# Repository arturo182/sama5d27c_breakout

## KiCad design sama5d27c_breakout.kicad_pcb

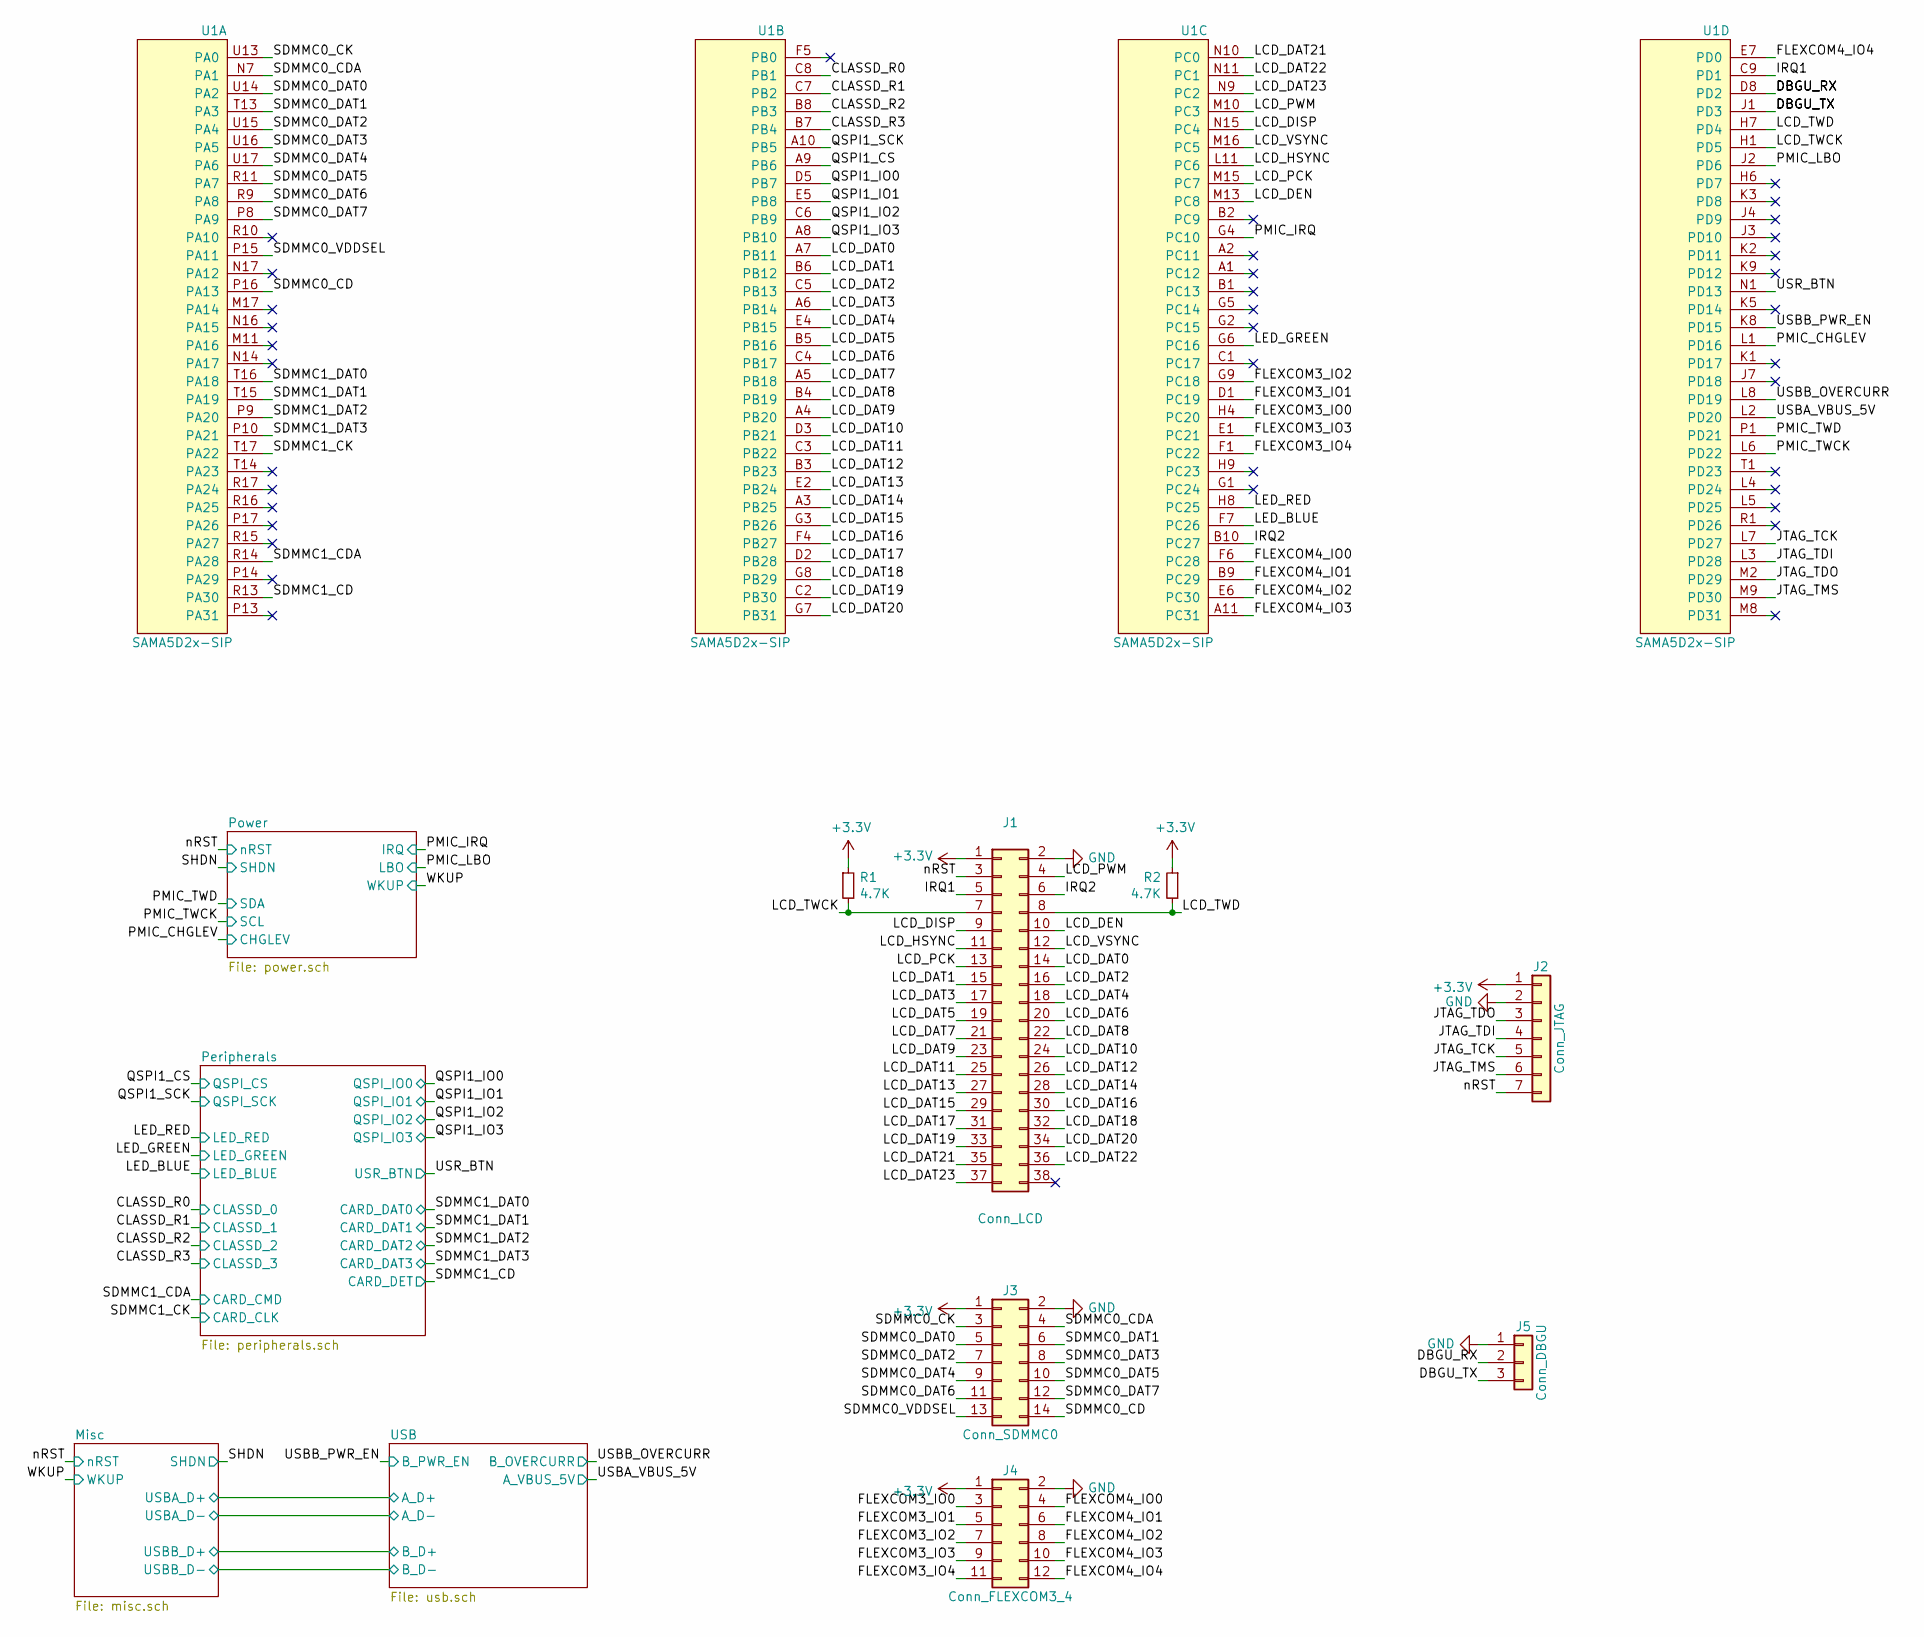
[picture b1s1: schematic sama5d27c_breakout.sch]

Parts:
J1: Conn_LCD; PinHeader_2x19_P1.27mm_Vertical_SMD
J2: Conn_JTAG; PinHeader_1x07_P2.54mm_Vertical
J3: Conn_SDMMC0; PinHeader_2x07_P2.54mm_Vertical
J4: Conn_FLEXCOM3_4; PinHeader_2x06_P2.54mm_Vertical
J5: Conn_DBGU; PinHeader_1x03_P2.54mm_Vertical
R1, R2: 4.7K; R_0603_1608Metric
U1: SAMA5D2x-SIP; TFBGA-289_17x17_14.0x14.0mm

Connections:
/CLASSD_R0: U1.C8 (PB1); also elsewhere on the board
/CLASSD_R1: U1.C7 (PB2); also elsewhere on the board
/CLASSD_R2: U1.B8 (PB3); also elsewhere on the board
/CLASSD_R3: U1.B7 (PB4); also elsewhere on the board
/DBGU_RX: J5.2, U1.D8 (PD2)
/DBGU_TX: J5.3, U1.J1 (PD3)
/FLEXCOM3_IO0: J4.3, U1.H4 (PC20)
/FLEXCOM3_IO1: J4.5, U1.D1 (PC19)
/FLEXCOM3_IO2: J4.7, U1.G9 (PC18)
/FLEXCOM3_IO3: J4.9, U1.E1 (PC21)
/FLEXCOM3_IO4: J4.11, U1.F1 (PC22)
/FLEXCOM4_IO0: J4.4, U1.F6 (PC28)
/FLEXCOM4_IO1: J4.6, U1.B9 (PC29)
/FLEXCOM4_IO2: J4.8, U1.E6 (PC30)
/FLEXCOM4_IO3: J4.10, U1.A11 (PC31)
/FLEXCOM4_IO4: J4.12, U1.E7 (PD0)
/IRQ1: J1.5, U1.C9 (PD1)
/IRQ2: J1.6, U1.B10 (PC27)
/JTAG_TCK: J2.5, U1.L7 (PD27)
/JTAG_TDI: J2.4, U1.L3 (PD28)
/JTAG_TDO: J2.3, U1.M2 (PD29)
/JTAG_TMS: J2.6, U1.M9 (PD30)
/LCD_DAT0: J1.14, U1.A7 (PB11)
/LCD_DAT1: J1.15, U1.B6 (PB12)
/LCD_DAT2: J1.16, U1.C5 (PB13)
/LCD_DAT3: J1.17, U1.A6 (PB14)
/LCD_DAT4: J1.18, U1.E4 (PB15)
/LCD_DAT5: J1.19, U1.B5 (PB16)
/LCD_DAT6: J1.20, U1.C4 (PB17)
/LCD_DAT7: J1.21, U1.A5 (PB18)
/LCD_DAT8: J1.22, U1.B4 (PB19)
/LCD_DAT9: J1.23, U1.A4 (PB20)
/LCD_DAT10: J1.24, U1.D3 (PB21)
/LCD_DAT11: J1.25, U1.C3 (PB22)
/LCD_DAT12: J1.26, U1.B3 (PB23)
/LCD_DAT13: J1.27, U1.E2 (PB24)
/LCD_DAT14: J1.28, U1.A3 (PB25)
/LCD_DAT15: J1.29, U1.G3 (PB26)
/LCD_DAT16: J1.30, U1.F4 (PB27)
/LCD_DAT17: J1.31, U1.D2 (PB28)
/LCD_DAT18: J1.32, U1.G8 (PB29)
/LCD_DAT19: J1.33, U1.C2 (PB30)
/LCD_DAT20: J1.34, U1.G7 (PB31)
/LCD_DAT21: J1.35, U1.N10 (PC0)
/LCD_DAT22: J1.36, U1.N11 (PC1)
/LCD_DAT23: J1.37, U1.N9 (PC2)
/LCD_DEN: J1.10, U1.M13 (PC8)
/LCD_DISP: J1.9, U1.N15 (PC4)
/LCD_HSYNC: J1.11, U1.L11 (PC6)
/LCD_PCK: J1.13, U1.M15 (PC7)
/LCD_PWM: J1.4, U1.M10 (PC3)
/LCD_TWCK: J1.7, R1.2, U1.H1 (PD5)
/LCD_TWD: J1.8, R2.2, U1.H7 (PD4)
/LCD_VSYNC: J1.12, U1.M16 (PC5)
/LED_BLUE: U1.F7 (PC26); also elsewhere on the board
/LED_GREEN: U1.G6 (PC16); also elsewhere on the board
/LED_RED: U1.H8 (PC25); also elsewhere on the board
/PMIC_CHGLEV: U1.L1 (PD16); also elsewhere on the board
/PMIC_IRQ: U1.G4 (PC10); also elsewhere on the board
/PMIC_LBO: U1.J2 (PD6); also elsewhere on the board
/PMIC_TWCK: U1.L6 (PD22); also elsewhere on the board
/PMIC_TWD: U1.P1 (PD21); also elsewhere on the board
/QSPI1_CS: U1.A9 (PB6); also elsewhere on the board
/QSPI1_IO0: U1.D5 (PB7); also elsewhere on the board
/QSPI1_IO1: U1.E5 (PB8); also elsewhere on the board
/QSPI1_IO2: U1.C6 (PB9); also elsewhere on the board
/QSPI1_IO3: U1.A8 (PB10); also elsewhere on the board
/QSPI1_SCK: U1.A10 (PB5); also elsewhere on the board
/SDMMC0_CD: J3.14, U1.P16 (PA13)
/SDMMC0_CDA: J3.4, U1.N7 (PA1)
/SDMMC0_CK: J3.3, U1.U13 (PA0)
/SDMMC0_DAT0: J3.5, U1.U14 (PA2)
/SDMMC0_DAT1: J3.6, U1.T13 (PA3)
/SDMMC0_DAT2: J3.7, U1.U15 (PA4)
/SDMMC0_DAT3: J3.8, U1.U16 (PA5)
/SDMMC0_DAT4: J3.9, U1.U17 (PA6)
/SDMMC0_DAT5: J3.10, U1.R11 (PA7)
/SDMMC0_DAT6: J3.11, U1.R9 (PA8)
/SDMMC0_DAT7: J3.12, U1.P8 (PA9)
/SDMMC0_VDDSEL: J3.13, U1.P15 (PA11)
/SDMMC1_CD: U1.R13 (PA30); also elsewhere on the board
/SDMMC1_CDA: U1.R14 (PA28); also elsewhere on the board
/SDMMC1_CK: U1.T17 (PA22); also elsewhere on the board
/SDMMC1_DAT0: U1.T16 (PA18); also elsewhere on the board
/SDMMC1_DAT1: U1.T15 (PA19); also elsewhere on the board
/SDMMC1_DAT2: U1.P9 (PA20); also elsewhere on the board
/SDMMC1_DAT3: U1.P10 (PA21); also elsewhere on the board
/USBA_VBUS_5V: U1.L2 (PD20); also elsewhere on the board
/USBB_OVERCURR: U1.L8 (PD19); also elsewhere on the board
/USBB_PWR_EN: U1.K8 (PD15); also elsewhere on the board
/USR_BTN: U1.N1 (PD13); also elsewhere on the board
/nRST: J1.3, J2.7; also elsewhere on the board
GND: J1.2, J2.2, J3.2, J4.2, J5.1; also elsewhere on the board

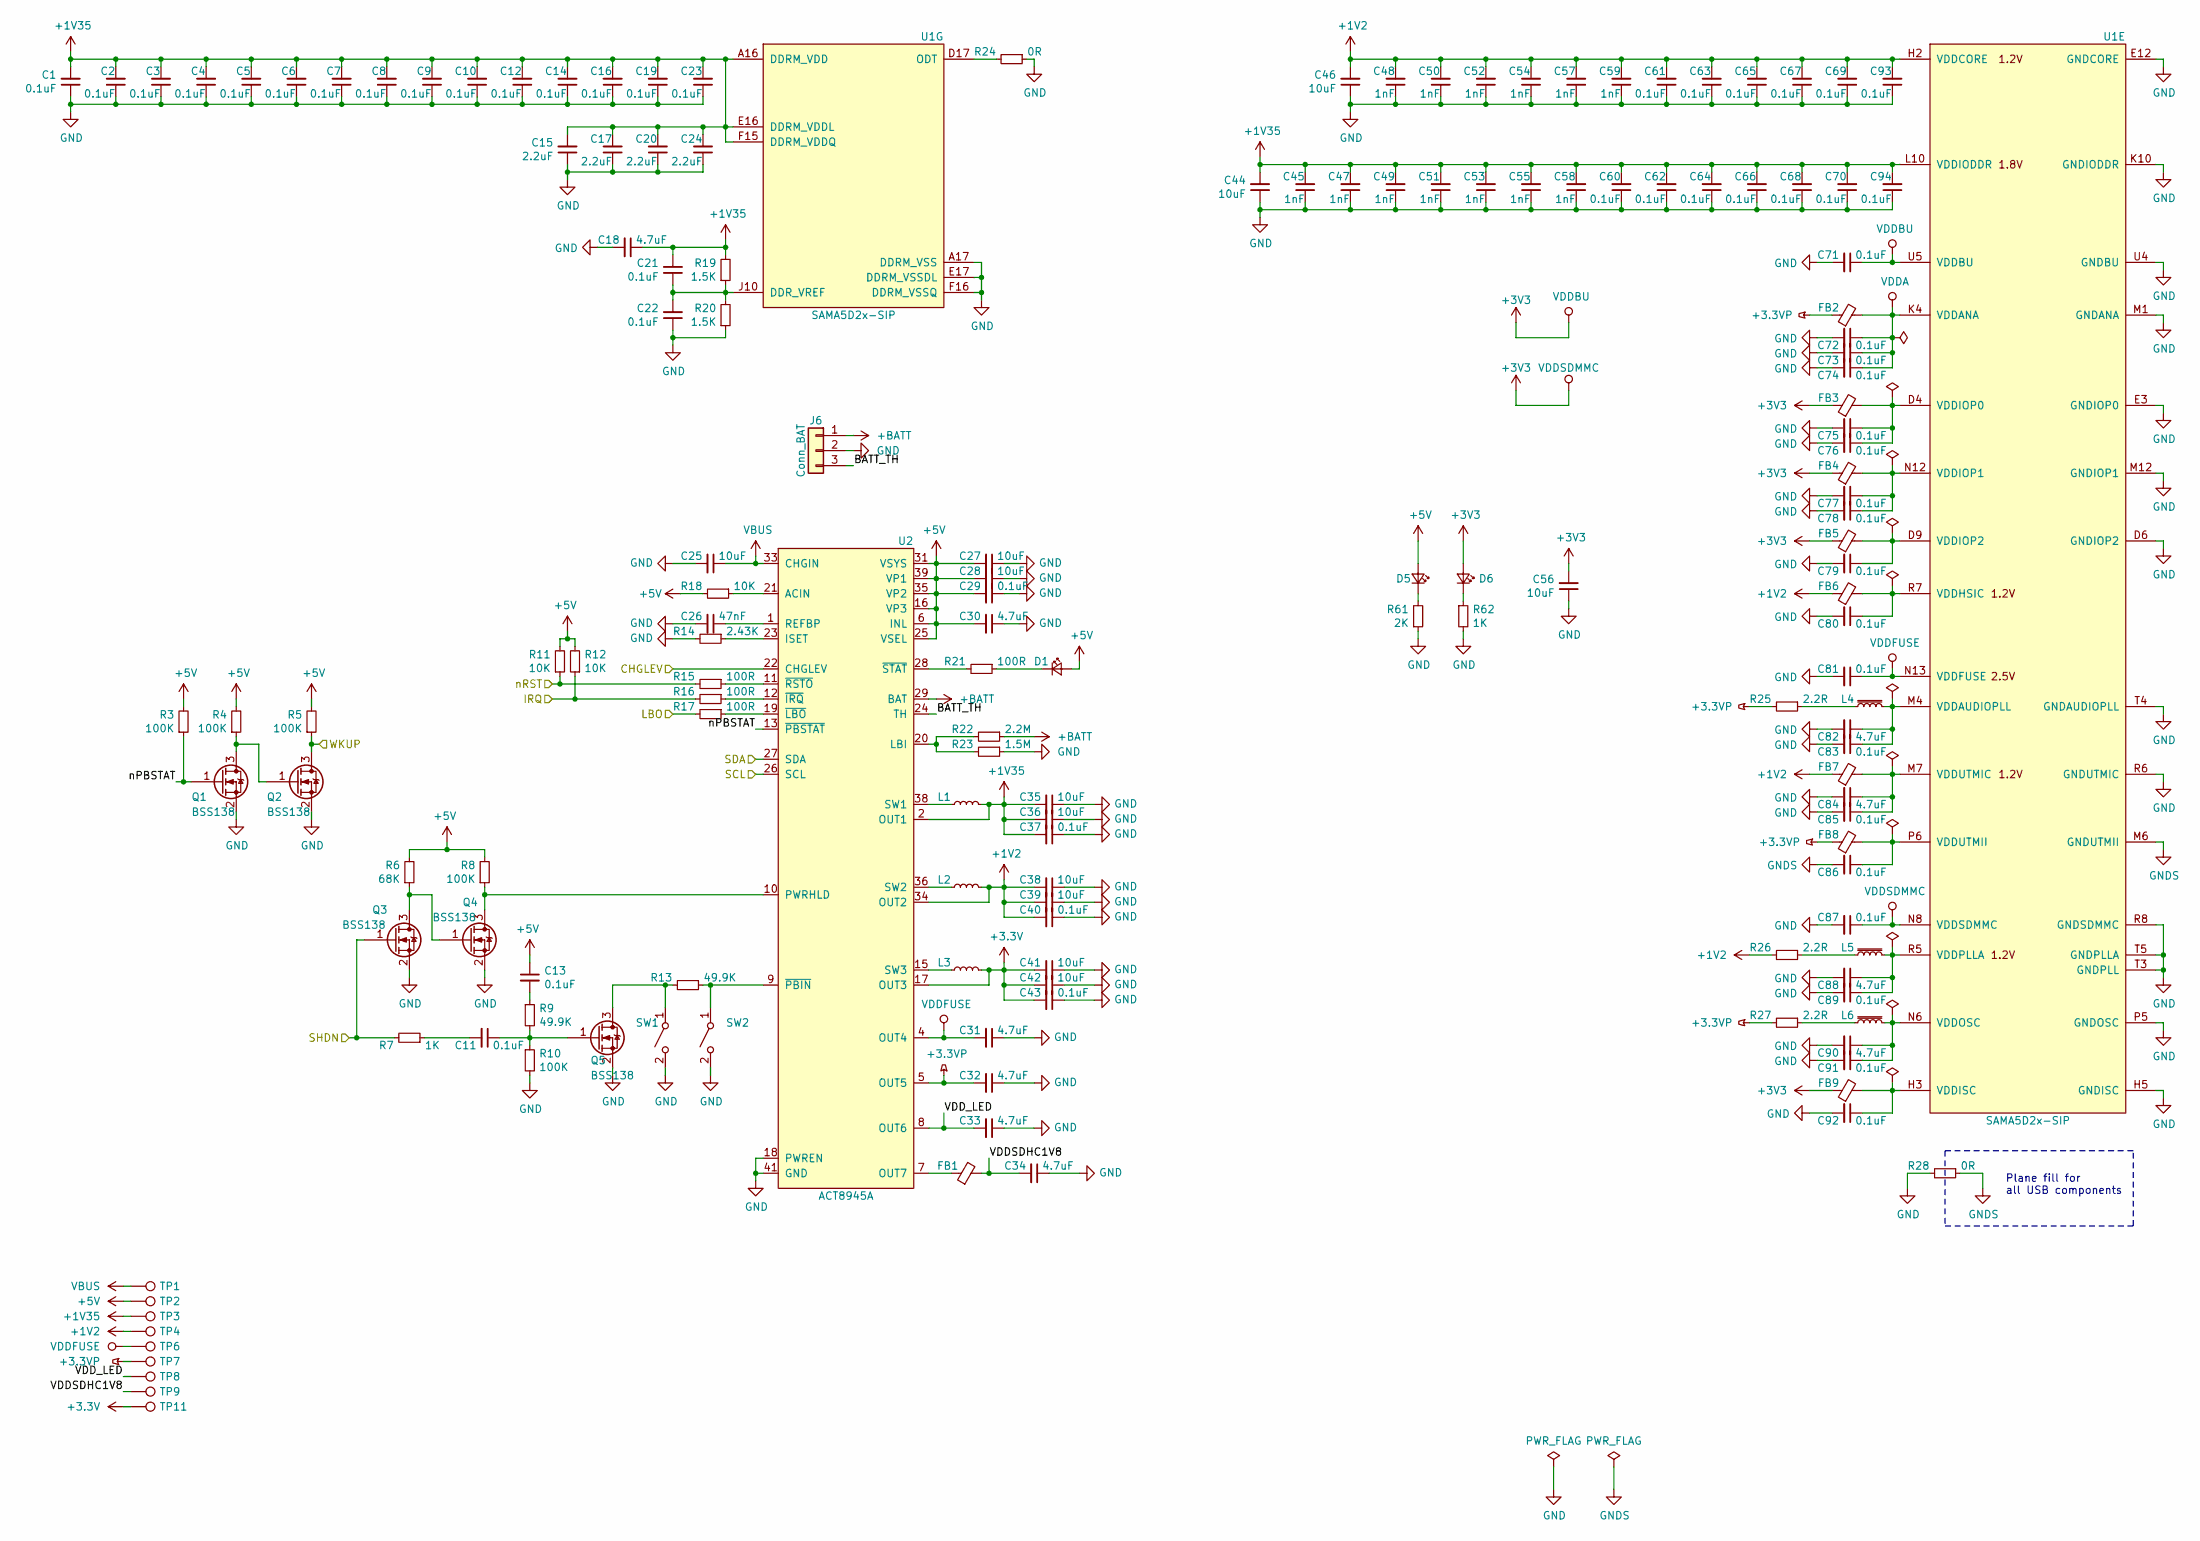
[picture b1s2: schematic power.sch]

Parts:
C1, C2, C3, C4, C5, C6, C7, C8, C9, C10, C11, C12, C13, C14, C16, C19, C21, C22, C23, C29, C37, C40, C43, C60, C61, C62, C63, C64, C65, C66, C67, C68, C69, C70, C71, C72, C73, C74, C75, C76, C77, C78, C79, C80, C81, C83, C85, C86, C87, C89, C91, C92, C93, C94: 0.1uF; C_0402_1005Metric
C15, C17, C20, C24: 2.2uF; C_0402_1005Metric
C18, C30, C31, C32, C33, C34, C82, C84, C88, C90: 4.7uF; C_0402_1005Metric
C25, C27, C28, C35, C36, C38, C39, C41, C42, C44, C46, C56: 10uF; C_0402_1005Metric
C26: 47nF; C_0402_1005Metric
C45, C47, C48, C49, C50, C51, C52, C53, C54, C55, C57, C58, C59: 1nF; C_0402_1005Metric
D1: LED_CHARGE; LED_0603_1608Metric
D5: LED_5V; LED_0603_1608Metric
D6: LED_3V; LED_0603_1608Metric
FB1: BLM18PG181SN1D; L_0603_1608Metric
FB2, FB3, FB4, FB5, FB6, FB7, FB8, FB9: BLM18PG300SN1D; L_0603_1608Metric
J6: Conn_BAT; PinHeader_1x03_P2.54mm_Vertical
L1, L2, L3: LQM2HPN2R2MG0L; L_Taiyo-Yuden_MD-3030
L4, L5, L6: MLZ1608N100L; L_0603_1608Metric
Q1, Q2, Q3, Q4, Q5: BSS138; SOT-23
R3, R4, R5, R8, R10: 100K; R_0603_1608Metric
R6: 68K; R_0603_1608Metric
R7, R62: 1K; R_0603_1608Metric
R9, R13: 49.9K; R_0603_1608Metric
R11, R12, R18: 10K; R_0603_1608Metric
R14: 2.43K; R_0603_1608Metric
R15, R16, R17, R21: 100R; R_0603_1608Metric
R19, R20: 1.5K; R_0603_1608Metric
R22: 2.2M; R_0603_1608Metric
R23: 1.5M; R_0603_1608Metric
R24, R28: 0R; R_0603_1608Metric
R25, R26, R27: 2.2R; R_0603_1608Metric
R61: 2K; R_0603_1608Metric
SW1: SW_WAKEUP; SW_SPST_FSMSM
SW2: SW_RESET; SW_SPST_FSMSM
TP1: TP_VBUS; TestPoint_Pad_D1.5mm
TP2: TP_5V; TestPoint_Pad_D1.5mm
TP3: TP_1.35V; TestPoint_Pad_D1.5mm
TP4: TP_1.2V; TestPoint_Pad_D1.5mm
TP6: TP_VDDFUSE; TestPoint_Pad_D1.5mm
TP7: TP_3.3VP; TestPoint_Pad_D1.5mm
TP8: TP_VDD_LED; TestPoint_Pad_D1.5mm
TP9: TP_VDDSDHC1V8; TestPoint_Pad_D1.5mm
TP11: TP_VDDSDMMC; TestPoint_Pad_D1.5mm
U1: SAMA5D2x-SIP; TFBGA-289_17x17_14.0x14.0mm
U2: ACT8945A; QFN-40-1EP_5x5mm_P0.4mm_EP3.6x3.6mm

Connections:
+1V2: C38.2, C39.2, C40.2, C46.2, C48.2, C50.2, C52.2, C54.2, C57.2, C59.2, C61.2, C63.2, C65.2, C67.2, C69.2, C93.2, FB6.1, FB7.1, L2.1, R26.2, TP4.1, U1.D7 (VDDCORE), U1.E9 (VDDCORE), U1.H2 (VDDCORE), U1.L12 (VDDCORE), U1.P7 (VDDCORE), U1.U3 (VDDCORE), U2.34 (OUT2)
+1V35: C1.2, C2.2, C3.2, C4.2, C5.2, C6.2, C7.2, C8.2, C9.2, C10.2, C12.2, C14.2, C15.2, C16.2, C17.2, C18.1, C19.2, C20.2, C21.2, C23.2, C24.2, C35.2, C36.2, C37.2, C44.2, C45.2, C47.2, C49.2, C51.2, C53.2, C55.2, C58.2, C60.2, C62.2, C64.2, C66.2, C68.2, C70.2, C94.2, L1.1, R19.2, TP3.1, U1.A16 (DDRM_VDD), U1.B16 (DDRM_VDD), U1.C16 (DDRM_VDD), U1.D16 (DDRM_VDD), U1.E8 (VDDIODDR), U1.E11 (VDDIODDR), U1.E15 (DDRM_VDD), U1.E16 (DDRM_VDDL), U1.F15 (DDRM_VDDQ), U1.G12 (VDDIODDR), U1.G15 (DDRM_VDDQ), U1.G17 (DDRM_VDD), U1.H10 (VDDIODDR), U1.H15 (DDRM_VDDQ), U1.J8 (VDDIODDR), U1.J15 (DDRM_VDDQ), U1.J17 (DDRM_VDD), U1.K15 (DDRM_VDDQ), U1.L10 (VDDIODDR), U1.L14 (VDDIODDR), U1.L15 (DDRM_VDDQ), U1.L16 (DDRM_VDD), U2.2 (OUT1)
+3.3VP: C32.2, FB2.1, FB8.1, R25.2, R27.2, TP7.1, U2.5 (OUT5)
+5V: C13.1, C27.2, C28.2, C29.2, C30.2, D1.2 (A), D5.2 (A), R3.2, R4.2, R5.2, R6.2, R8.2, R11.2, R12.2, R18.2, TP2.1, U2.6 (INL), U2.16 (VP3), U2.25 (VSEL), U2.31 (VSYS), U2.32 (VSYS), U2.35 (VP2), U2.39 (VP1); also elsewhere on the board
+BATT: J6.1, R22.1, U2.29 (BAT), U2.30 (BAT)
/PMIC_CHGLEV: U2.22 (CHGLEV); also elsewhere on the board
/PMIC_IRQ: R12.1, R16.2; also elsewhere on the board
/PMIC_LBO: R17.2; also elsewhere on the board
/PMIC_TWCK: U2.26 (SCL); also elsewhere on the board
/PMIC_TWD: U2.27 (SDA); also elsewhere on the board
/Power/BATT_TH: J6.3, U2.24 (TH)
/Power/VDDSDHC1V8: C34.2, FB1.2, TP9.1
/Power/VDD_LED: C33.2, TP8.1, U2.8 (OUT6)
/Power/nPBSTAT: Q1.1 (G), R3.1, U2.13 (~PBSTAT~)
/SHDN: Q3.1 (G), R7.2; also elsewhere on the board
/WKUP: Q2.3 (D), R5.1; also elsewhere on the board
/nRST: R11.1, R15.2; also elsewhere on the board
GND: C1.1, C2.1, C3.1, C4.1, C5.1, C6.1, C7.1, C8.1, C9.1, C10.1, C12.1, C14.1, C15.1, C16.1, C17.1, C18.2, C19.1, C20.1, C22.1, C23.1, C24.1, C25.2, C26.2, C27.1, C28.1, C29.1, C30.1, C31.1, C32.1, C33.1, C34.1, C35.1, C36.1, C37.1, C38.1, C39.1, C40.1, C41.1, C42.1, C43.1, C44.1, C45.1, C46.1, C47.1, C48.1, C49.1, C50.1, C51.1, C52.1, C53.1, C54.1, C55.1, C56.1, C57.1, C58.1, C59.1, C60.1, C61.1, C62.1, C63.1, C64.1, C65.1, C66.1, C67.1, C68.1, C69.1, C70.1, C71.2, C72.2, C73.2, C74.2, C75.2, C76.2, C77.2, C78.2, C79.2, C80.2, C81.2, C82.2, C83.2, C84.2, C85.2, C87.2, C88.2, C89.2, C90.2, C91.2, C92.2, C93.1, C94.1, J6.2, Q1.2 (S), Q2.2 (S), Q3.2 (S), Q4.2 (S), Q5.2 (S), R10.2, R14.2, R20.1, R23.1, R24.1, R28.2, R61.1, R62.2, SW1.2 (B), SW2.2 (B), U1.A17 (DDRM_VSS), U1.B17 (DDRM_VSS), U1.C17 (DDRM_VSS), U1.D6 (GNDIOP2), U1.D15 (DDRM_VSS), U1.E3 (GNDIOP0), U1.E10 (GNDIODDR), U1.E12 (GNDCORE), U1.E14 (DDRM_VSS), U1.E17 (DDRM_VSSDL), U1.F2 (GNDIOP0), U1.F8 (GNDIODDR), U1.F12 (GNDCORE), U1.F16 (DDRM_VSSQ), U1.F17 (DDRM_VSS), U1.G10 (GNDIODDR), U1.G16 (DDRM_VSSQ), U1.H5 (GNDISC), U1.H12 (GNDIODDR), U1.H16 (DDRM_VSSQ), U1.H17 (DDRM_VSS), U1.J6 (GNDANA), U1.J9 (GNDIODDR), U1.J11 (GNDCORE), U1.J16 (DDRM_VSSQ), U1.K6 (GNDCORE), U1.K7 (GNDCORE), U1.K10 (GNDIODDR), U1.K11 (GNDCORE), U1.K16 (DDRM_VSSQ), U1.K17 (DDRM_VSSQ), U1.L17 (DDRM_VSS), U1.M1 (GNDANA), U1.M12 (GNDIOP1), U1.M14 (GNDIODDR), U1.P5 (GNDOSC), U1.P11 (GNDIOP1), U1.R6 (GNDUTMIC), U1.R8 (GNDSDMMC), U1.T3 (GNDPLL), U1.T4 (GNDAUDIOPLL), U1.T5 (GNDPLLA), U1.U4 (GNDBU), U2.3 (GA), U2.14 (GP3), U2.18 (PWREN), U2.37 (GP12), U2.41 (GND); also elsewhere on the board
GNDS: C86.2, R28.1, U1.M6 (GNDUTMII); also elsewhere on the board
unnamed: C11.1, Q5.1 (G), R9.2, R10.1
unnamed: C11.2, R7.1
unnamed: C13.2, R9.1
unnamed: C21.1, C22.2, R19.1, R20.2, U1.F11 (DDR_VREF), U1.J10 (DDR_VREF)
unnamed: C26.1, U2.1 (REFBP)
unnamed: C75.1, C76.1, FB3.2, U1.D4 (VDDIOP0), U1.F3 (VDDIOP0)
unnamed: C77.1, C78.1, FB4.2, U1.N12 (VDDIOP1), U1.P12 (VDDIOP1)
unnamed: C79.1, FB5.2, U1.D9 (VDDIOP2)
unnamed: C80.1, FB6.2, U1.R7 (VDDHSIC)
unnamed: C82.1, C83.1, L4.2, U1.M4 (VDDAUDIOPLL)
unnamed: C84.1, C85.1, FB7.2, U1.M7 (VDDUTMIC)
unnamed: C86.1, FB8.2, U1.P6 (VDDUTMII)
unnamed: C88.1, C89.1, L5.2, U1.R5 (VDDPLLA)
unnamed: C90.1, C91.1, L6.2, U1.N6 (VDDOSC)
unnamed: C92.1, FB9.2, U1.H3 (VDDISC)
unnamed: D1.1 (K), R21.1
unnamed: D5.1 (K), R61.2
unnamed: D6.1 (K), R62.1
unnamed: FB1.1, U2.7 (OUT7)
unnamed: L1.2, U2.38 (SW1)
unnamed: L2.2, U2.36 (SW2)
unnamed: L3.2, U2.15 (SW3)
unnamed: L4.1, R25.1
unnamed: L5.1, R26.1
unnamed: L6.1, R27.1
unnamed: Q1.3 (D), Q2.1 (G), R4.1
unnamed: Q3.3 (D), Q4.1 (G), R6.1
unnamed: Q4.3 (D), R8.1, U2.10 (PWRHLD)
unnamed: Q5.3 (D), R13.2, SW1.1 (A)
unnamed: R13.1, SW2.1 (A), U2.9 (~PBIN~)
unnamed: R14.1, U2.23 (ISET)
unnamed: R15.1, U2.11 (~RSTO~)
unnamed: R16.1, U2.12 (~IRQ~)
unnamed: R17.1, U2.19 (~LBO~)
unnamed: R18.1, U2.21 (ACIN)
unnamed: R21.2, U2.28 (~STAT~)
unnamed: R22.2, R23.2, U2.20 (LBI)
unnamed: R24.2, U1.D17 (ODT)
VBUS: C25.1, TP1.1, U2.33 (CHGIN); also elsewhere on the board
VDDA: C72.1, C73.1, C74.1, FB2.2, U1.J5 (VDDANA), U1.K4 (VDDANA); also elsewhere on the board
VDDFUSE: C31.2, C81.1, TP6.1, U1.N13 (VDDFUSE), U2.4 (OUT4)

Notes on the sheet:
Plane fill for all USB components

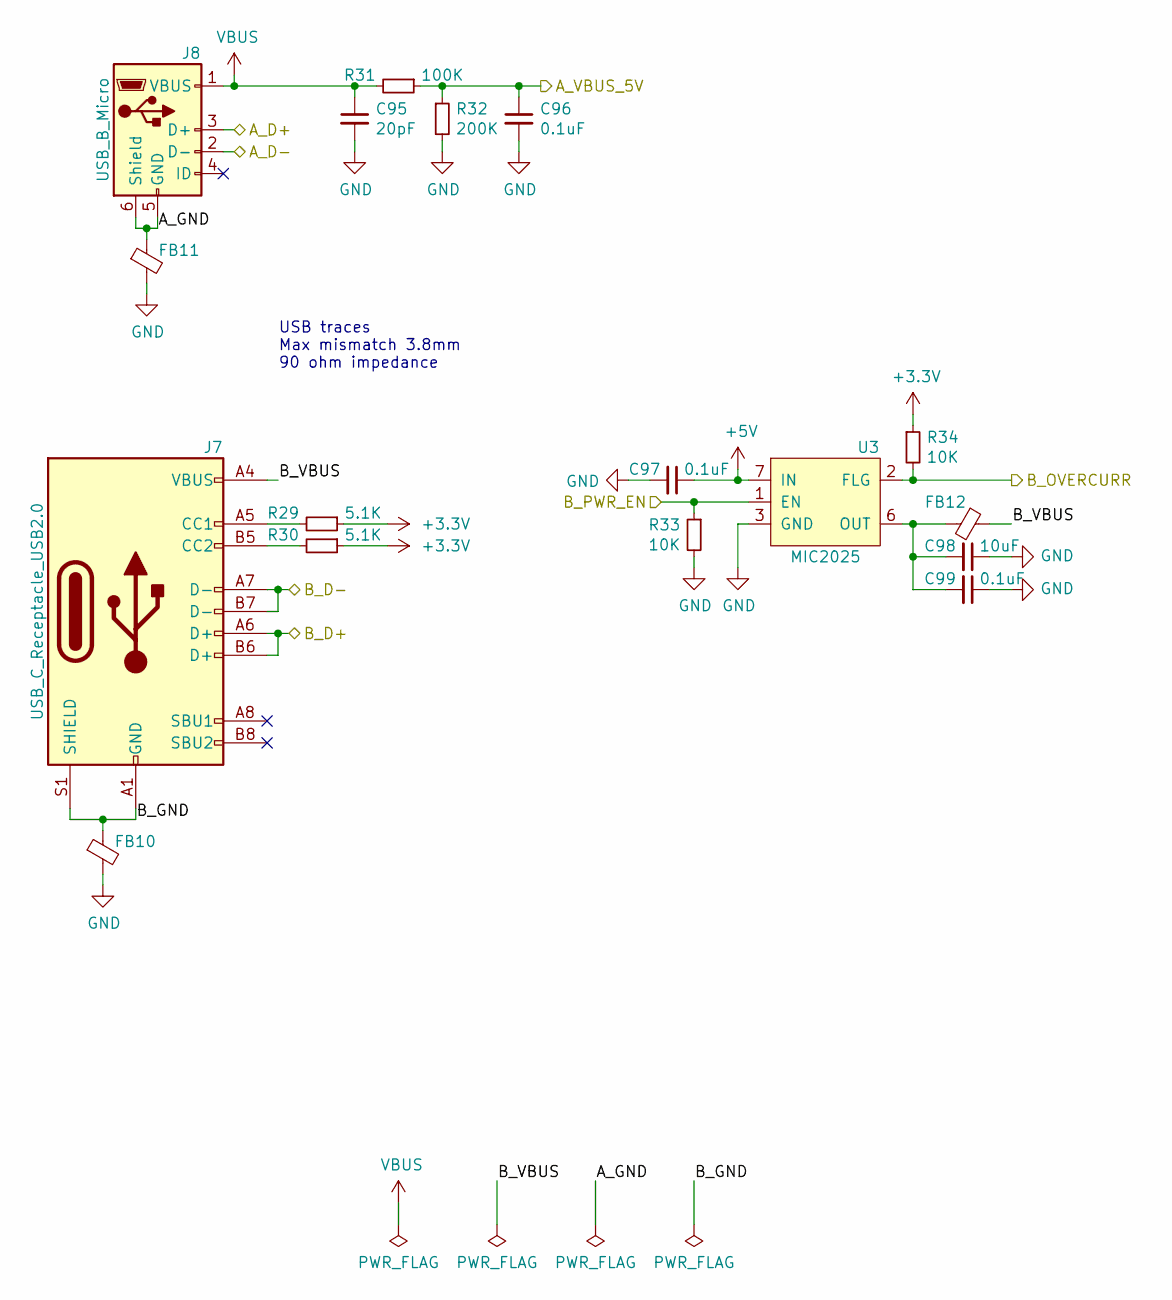
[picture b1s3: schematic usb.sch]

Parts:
C95: 20pF; C_0402_1005Metric
C96, C97, C99: 0.1uF; C_0402_1005Metric
C98: 10uF; C_0402_1005Metric
FB10, FB11, FB12: BLM18PG300SN1D; L_0603_1608Metric
J7: USB_C_Receptacle_USB2.0; USB_C_Receptacle_GT-USB-7010
J8: USB_B_Micro; USB_Micro-B_Molex-105017-0001
R29, R30: 5.1K; R_0603_1608Metric
R31: 100K; R_0603_1608Metric
R32: 200K; R_0603_1608Metric
R33, R34: 10K; R_0603_1608Metric
U3: MIC2025; SOIC-8_3.9x4.9mm_P1.27mm

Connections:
+5V: C97.1, U3.7 (IN); also elsewhere on the board
/USB/A_D+: J8.3 (D+); also elsewhere on the board
/USB/A_D-: J8.2 (D-); also elsewhere on the board
/USB/A_GND: FB11.1, J8.5 (GND), J8.6 (Shield)
/USB/B_D+: J7.A6 (D+), J7.B6 (D+); also elsewhere on the board
/USB/B_D-: J7.A7 (D-), J7.B7 (D-); also elsewhere on the board
/USB/B_GND: FB10.1, J7.A1 (GND), J7.A12 (GND), J7.B1 (GND), J7.B12 (GND), J7.S1 (SHIELD)
/USB/B_VBUS: FB12.1, J7.A4 (VBUS), J7.A9 (VBUS), J7.B4 (VBUS), J7.B9 (VBUS)
/USBA_VBUS_5V: C96.1, R31.1, R32.1; also elsewhere on the board
/USBB_OVERCURR: R34.2, U3.2 (FLG); also elsewhere on the board
/USBB_PWR_EN: R33.1, U3.1 (EN); also elsewhere on the board
GND: C95.2, C96.2, C97.2, C98.1, C99.1, FB10.2, FB11.2, R32.2, R33.2, U3.3 (GND); also elsewhere on the board
unnamed: C98.2, C99.2, FB12.2, U3.6 (OUT), U3.8 (OUT)
unnamed: J7.A5 (CC1), R29.2
unnamed: J7.B5 (CC2), R30.2
VBUS: C95.1, J8.1 (VBUS), R31.2; also elsewhere on the board

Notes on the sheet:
USB traces Max mismatch 3.8mm 90 ohm impedance

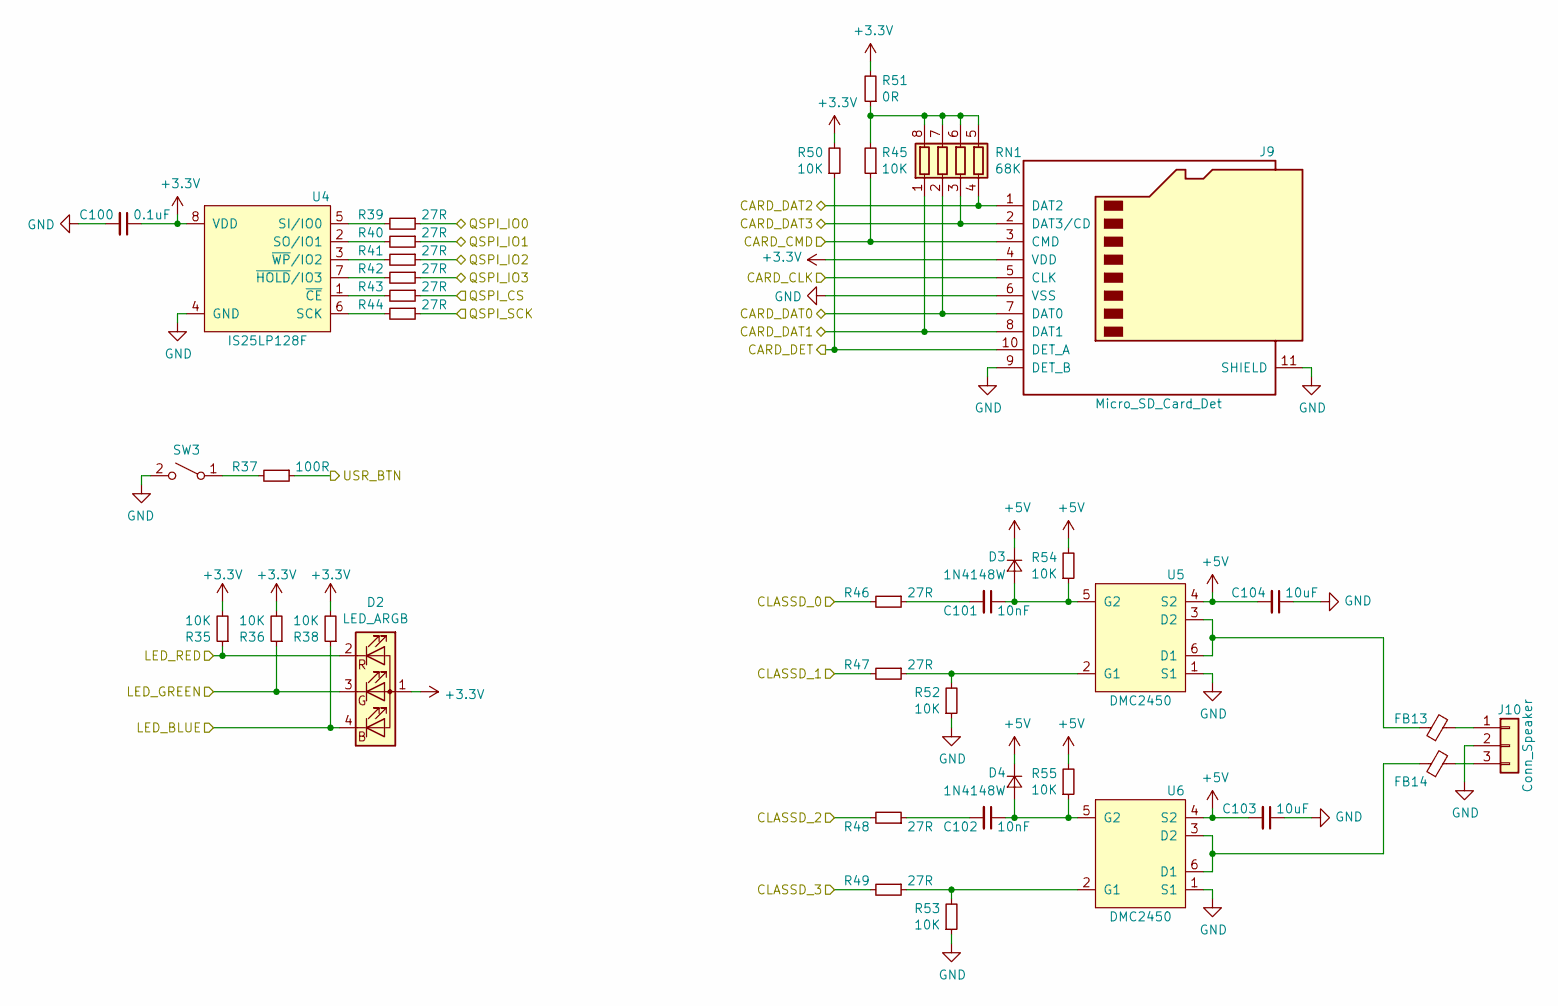
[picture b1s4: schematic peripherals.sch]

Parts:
C100: 0.1uF; C_0402_1005Metric
C101, C102: 10nF; C_0402_1005Metric
C103, C104: 10uF; C_0402_1005Metric
D2: LED_ARGB; LED_RGB_0606_1616Metric
D3, D4: 1N4148W; D_SOD-123
FB13, FB14: BLM18PG300SN1D; L_0603_1608Metric
J9: Micro_SD_Card_Det; microSD_HC_Molex_104031-0811
J10: Conn_Speaker; PinHeader_1x03_P2.54mm_Vertical
R35, R36, R38, R45, R50, R52, R53, R54, R55: 10K; R_0603_1608Metric
R37: 100R; R_0603_1608Metric
R39, R40, R41, R42, R43, R44, R46, R47, R48, R49: 27R; R_0603_1608Metric
R51: 0R; R_0603_1608Metric
RN1: 68K; R_Array_Concave_4x0603
SW3: SW_USR; SW_SPST_FSMSM
U4: IS25LP128F; WSON-8-1EP_6x5mm_P1.27mm_EP3.4x4mm
U5, U6: DMC2450; SOT-563

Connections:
+5V: C103.2, C104.2, D3.1 (K), D4.1 (K), R54.2, R55.2, U5.4 (S2), U6.4 (S2); also elsewhere on the board
/CLASSD_R0: R46.2; also elsewhere on the board
/CLASSD_R1: R47.2; also elsewhere on the board
/CLASSD_R2: R48.2; also elsewhere on the board
/CLASSD_R3: R49.2; also elsewhere on the board
/LED_BLUE: D2.4 (BK), R38.1; also elsewhere on the board
/LED_GREEN: D2.3 (GK), R36.1; also elsewhere on the board
/LED_RED: D2.2 (RK), R35.1; also elsewhere on the board
/QSPI1_CS: R43.1; also elsewhere on the board
/QSPI1_IO0: R39.1; also elsewhere on the board
/QSPI1_IO1: R40.1; also elsewhere on the board
/QSPI1_IO2: R41.1; also elsewhere on the board
/QSPI1_IO3: R42.1; also elsewhere on the board
/QSPI1_SCK: R44.1; also elsewhere on the board
/SDMMC1_CD: J9.10 (DET_A), R50.1; also elsewhere on the board
/SDMMC1_CDA: J9.3 (CMD), R45.1; also elsewhere on the board
/SDMMC1_CK: J9.5 (CLK); also elsewhere on the board
/SDMMC1_DAT0: J9.7 (DAT0), RN1.2 (R2.1); also elsewhere on the board
/SDMMC1_DAT1: J9.8 (DAT1), RN1.1 (R1.1); also elsewhere on the board
/SDMMC1_DAT2: J9.1 (DAT2), RN1.4 (R4.1); also elsewhere on the board
/SDMMC1_DAT3: J9.2 (DAT3/CD), RN1.3 (R3.1); also elsewhere on the board
/USR_BTN: R37.1; also elsewhere on the board
GND: C100.2, C103.1, C104.1, J9.6 (VSS), J9.9 (DET_B), J9.11 (SHIELD), J10.2, R52.1, R53.1, SW3.2 (B), U4.4 (GND), U4.9 (GND), U5.1 (S1), U6.1 (S1); also elsewhere on the board
unnamed: C101.1, D3.2 (A), R54.1, U5.5 (G2)
unnamed: C101.2, R46.1
unnamed: C102.1, D4.2 (A), R55.1, U6.5 (G2)
unnamed: C102.2, R48.1
unnamed: FB13.1, U5.3 (D2), U5.6 (D1)
unnamed: FB13.2, J10.1
unnamed: FB14.1, U6.3 (D2), U6.6 (D1)
unnamed: FB14.2, J10.3
unnamed: R37.2, SW3.1 (A)
unnamed: R39.2, U4.5 (SI/IO0)
unnamed: R40.2, U4.2 (SO/IO1)
unnamed: R41.2, U4.3 (~WP~/IO2)
unnamed: R42.2, U4.7 (~HOLD~/IO3)
unnamed: R43.2, U4.1 (~CE~)
unnamed: R44.2, U4.6 (SCK)
unnamed: R45.2, R51.1, RN1.5 (R4.2), RN1.6 (R3.2), RN1.7 (R2.2), RN1.8 (R1.2)
unnamed: R47.1, R52.2, U5.2 (G1)
unnamed: R49.1, R53.2, U6.2 (G1)

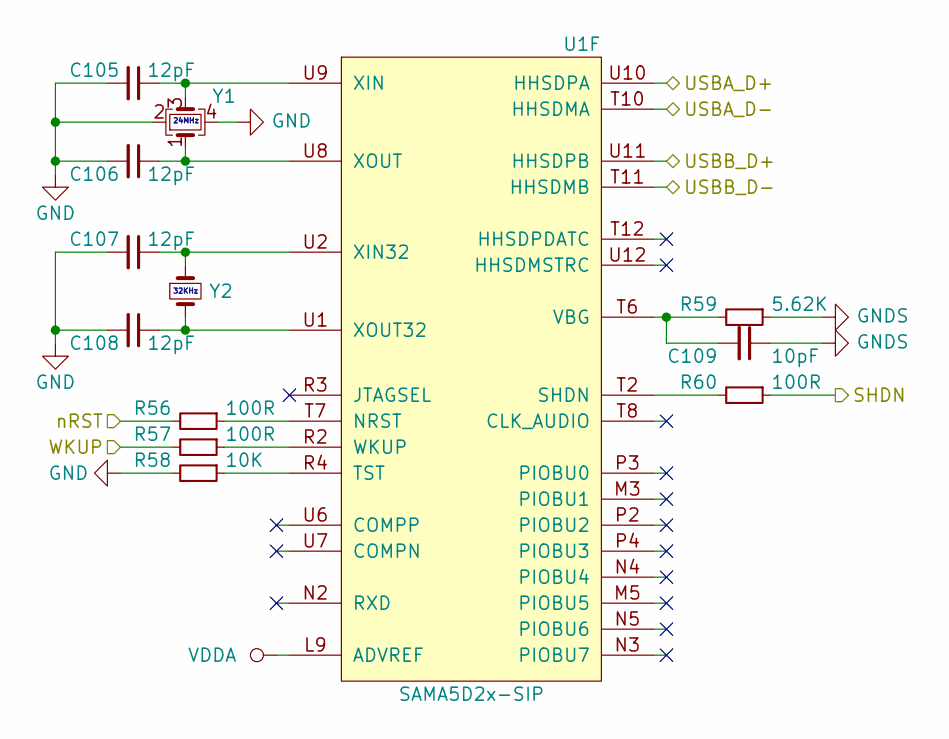
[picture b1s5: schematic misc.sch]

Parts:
C105, C106, C107, C108: 12pF; C_0402_1005Metric; Voltage 50V
C109: 10pF; C_0402_1005Metric
R56, R57, R60: 100R; R_0603_1608Metric
R58: 10K; R_0603_1608Metric
R59: 5.62K; R_0603_1608Metric
U1: SAMA5D2x-SIP; TFBGA-289_17x17_14.0x14.0mm
Y1: TSX-3225 24MHz; Crystal_SMD_3225-4Pin_3.2x2.5mm
Y2: 32kHz; Crystal_SMD_3215-2Pin_3.2x1.5mm

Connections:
/SHDN: R60.1; also elsewhere on the board
/USB/A_D+: U1.U10 (HHSDPA); also elsewhere on the board
/USB/A_D-: U1.T10 (HHSDMA); also elsewhere on the board
/USB/B_D+: U1.U11 (HHSDPB); also elsewhere on the board
/USB/B_D-: U1.T11 (HHSDMB); also elsewhere on the board
/WKUP: R57.2; also elsewhere on the board
/nRST: R56.2; also elsewhere on the board
GND: C105.2, C106.2, C107.2, C108.2, R58.2, Y1.2, Y1.4; also elsewhere on the board
GNDS: C109.1, R59.1; also elsewhere on the board
unnamed: C105.1, U1.U9 (XIN), Y1.3
unnamed: C106.1, U1.U8 (XOUT), Y1.1
unnamed: C107.1, U1.U2 (XIN32), Y2.1
unnamed: C108.1, U1.U1 (XOUT32), Y2.2
unnamed: C109.2, R59.2, U1.T6 (VBG)
unnamed: R56.1, U1.T7 (NRST)
unnamed: R57.1, U1.R2 (WKUP)
unnamed: R58.1, U1.R4 (TST)
unnamed: R60.2, U1.T2 (SHDN)
VDDA: U1.L9 (ADVREF); also elsewhere on the board

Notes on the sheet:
24MHz
32KHz

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
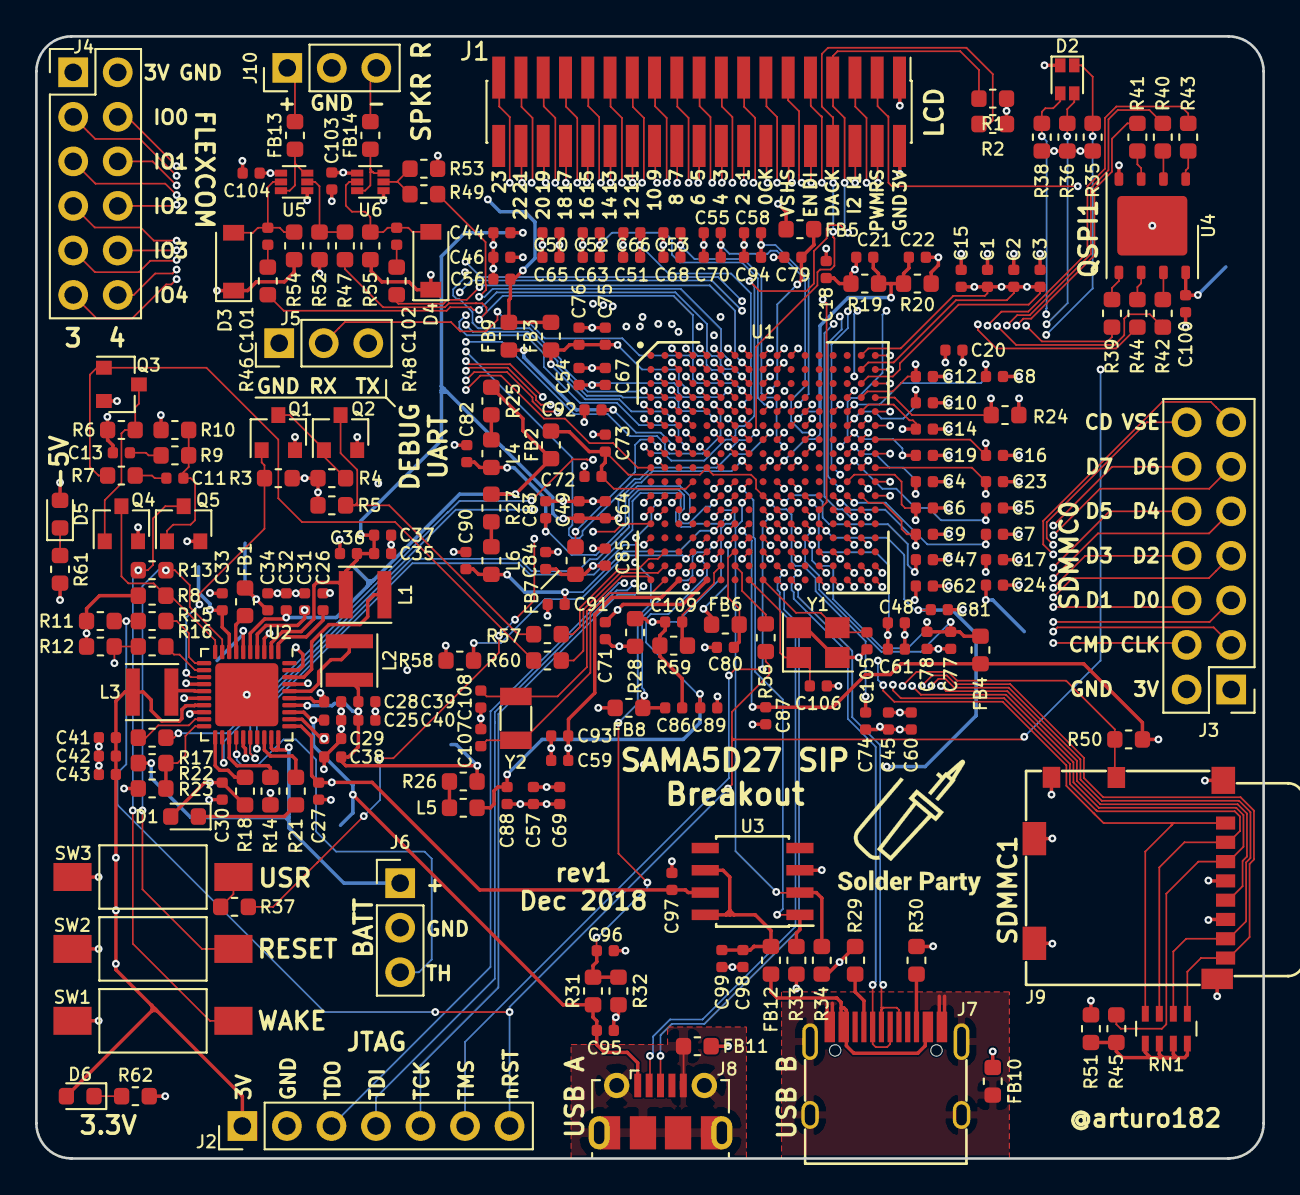
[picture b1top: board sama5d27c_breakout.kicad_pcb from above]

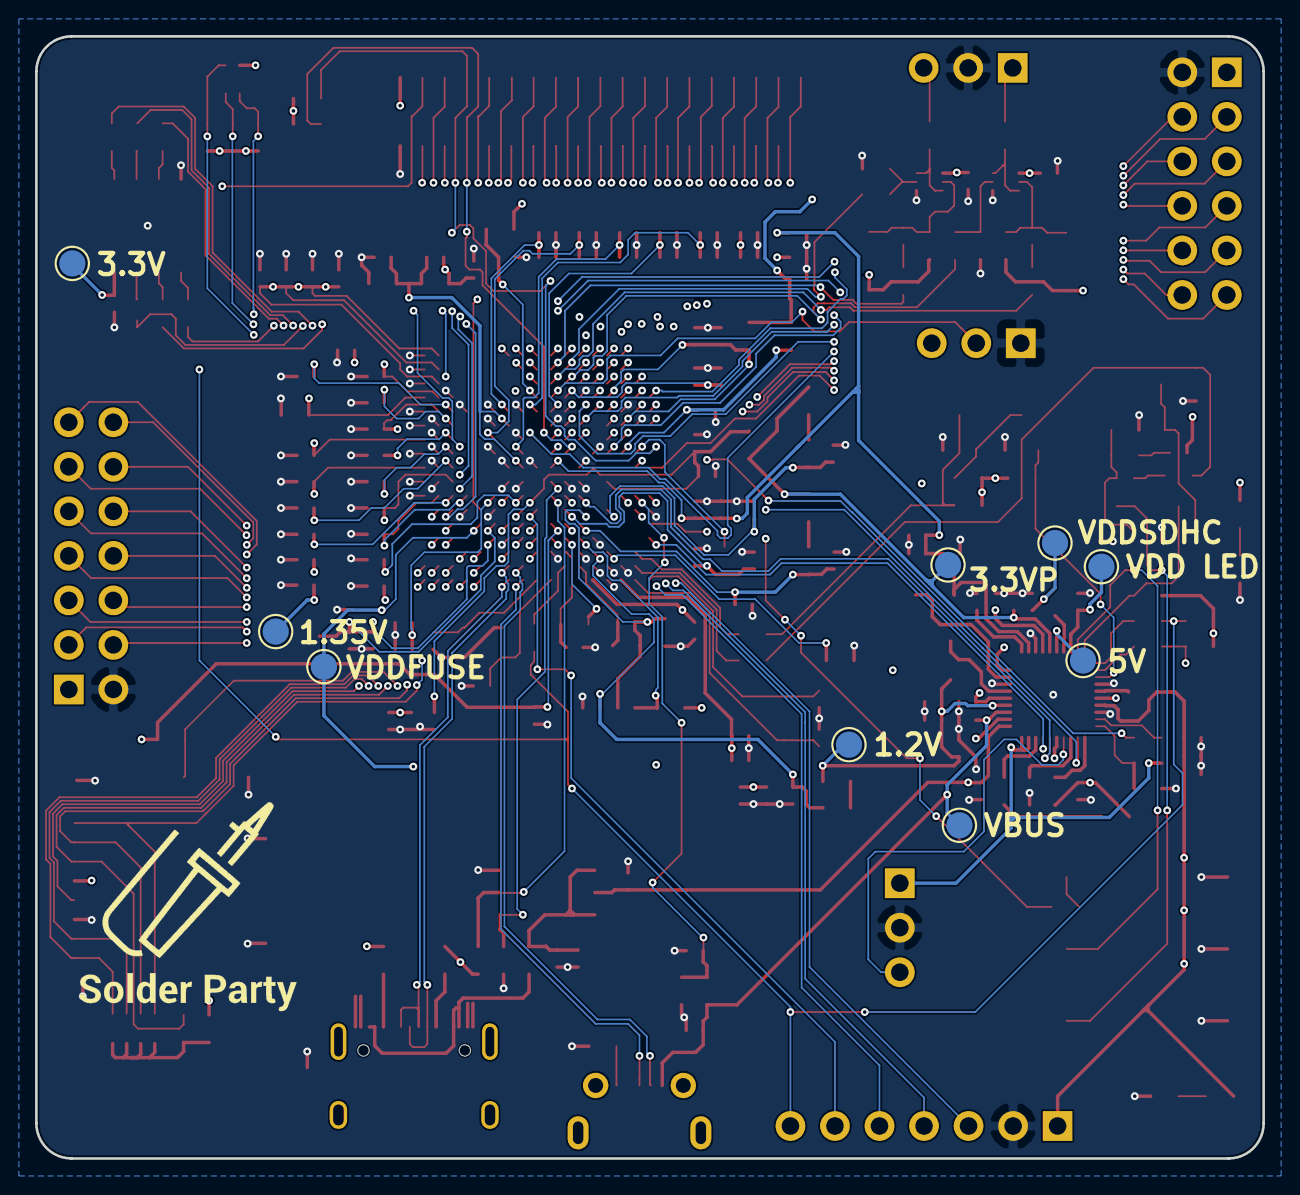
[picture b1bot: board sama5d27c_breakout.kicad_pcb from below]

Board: 4 copper layers, 70.0 x 64.0 mm, 233 parts (9 on the bottom side), 184 nets.
